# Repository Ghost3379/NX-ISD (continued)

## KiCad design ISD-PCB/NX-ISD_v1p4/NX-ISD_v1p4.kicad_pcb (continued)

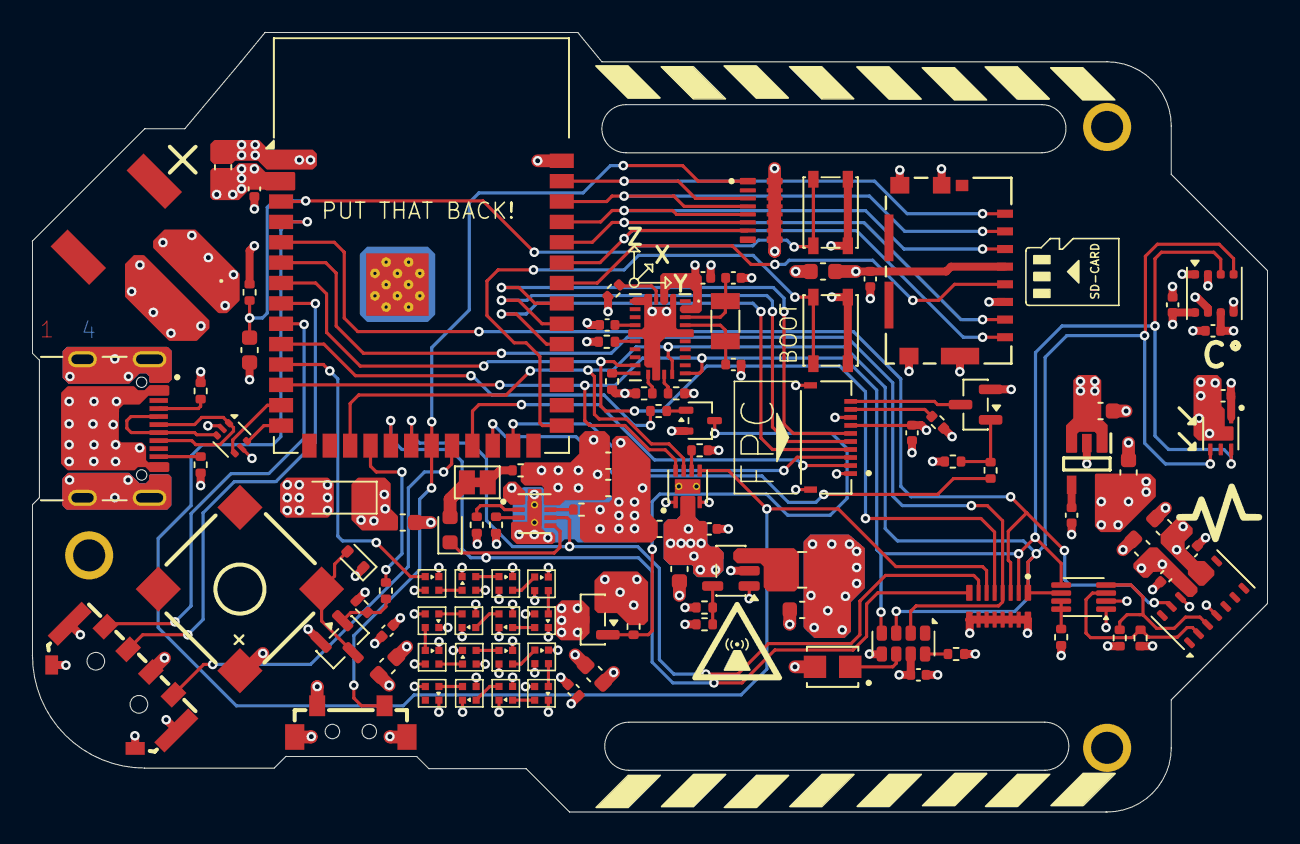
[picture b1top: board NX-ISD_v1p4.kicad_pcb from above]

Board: 4 copper layers, 77.0 x 48.6 mm, 109 parts (0 on the bottom side), 86 nets.

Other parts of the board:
XYZ: n/a; XYZ_DOF_symbol

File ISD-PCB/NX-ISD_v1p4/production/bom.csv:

Designator,Footprint,Quantity,Value,LCSC Part #
B1,BUZ-SMD_4P-L8.5-W8.5-BR-1,1,SMD-8503-3627-16Ω,C2685545
"C1, C10, C16, C26, C4, C9",0603,6,1u,
"C11, C24, C27, C33, C6",0603,5,10u,
"C12, C13, C17, C18, C19, C20, C21, C25, C28, C29, C30, C31, C34, C36",0402,14,100n,
"C2, C32, C35, C37",0603,4,4.7u,
"C22, C23",0402,2,22p,
C3,0402,1,10n,
C5,CAPCP3225X100N,1,CPH3225A,
D1,D_SOD-123,1,NRVB230LSFT1G,
D2,0603,1,ORANGE,
D3,D_SOD-523,1,1N4148WT,
"G1, G10, G11, G12, G13, G14, G15, G16, G2, G3, G4, G5, G6, G7, G8, G9",LED-SMD_4P-L1.0-W1.0-TL_XL-1010RGBC-WS2812B,16,XL-1010RGBC-WS2812B,C5349953
J1,SAMESKY_UJ20-C-H-G-SMT-1-P16-TR,1,UJ20-C-H-G-SMT-1-P16-TR,
J2,TE_1-2328702-0,1,1-2328702-0,
J3,105162-0001_MOL,1,1051620001,
L1,1008,1,2.2u,
P1,JST_S2B-PH-SM4-TB,1,S2B-PH-SM4-TB,
Q1,SOT-323_SC-70,1,BC847W,
Q2,SOT-23,1,AO3401A,
"Q3, Q4",SOT-23,2,AO3400A,
"R1, R2",0402,2,5.1k,
"R10, R4",0402,2,100K,
"R11, R12",0402,2,4.7k,
"R13, R14, R16, R17, R18, R19, R24, R26, R29, R8",0402,10,10k,
R15,0402,1,200k,
"R23, R25",0402,2,220,
R27,0402,1,10,
R3,0402,1,453k,
R5,0402,1,27k,
R6,0402,1,499,
"R7, R9",0402,2,1k,
"RN1, RN2",RESCAXS50P400X160X55-16N,2,YC248-JR-074K7L,
S1,KEY-SMD_TS-1101VS-C-A-A,1,TS-1101VS-C-A-A,
S2,SW-SMD_TM-2025A,1,TM-2025A,C318949
SW1,SW_SPST_PTS810,1,BOOT,
SW2,SW_SPST_PTS810,1,RST,
TH1,0402,1,10k NTC,
U1,SOT23-5,1,RT9193-18GB,C27416
U10,SON65P200X200X65-7N,1,OPT3001DNPR,
U11,IC_BNO085,1,BNO085,
U12,MicroCrystal_C7_SON-8_1.5x3.2mm_P0.9mm,1,RV-3028-C7,
U13,ESP32-S3-WROOM-1,1,ESP32-S3-WROOM-1-N16R8,ESP32-S3-WROOM-1-N16R8
U2,SOT-666,1,USBLC6-2P6,
U3,SOT-23-5,1,TLV62568DBV,
U5,SON50P200X200X80-9N,1,BQ25170DSGR,
U6,SON50P200X200X80-9N,1,MAX17048G_T10,
U7,Bosch_LGA-8_3x3mm_P0.8mm_ClockwisePinNumbering,1,BME690,
U8,Maxim_OLGA-14_3.3x5.6mm_P0.8mm,1,MAX30102,
U9,VSSOP-8_2.3x2mm_P0.5mm,1,PCA9306,
XYZ,XYZ_DOF_symbol,1,n/a,
Y1,Crystal_SMD_3215-2Pin_3.2x1.5mm,1,32.768 kHz,

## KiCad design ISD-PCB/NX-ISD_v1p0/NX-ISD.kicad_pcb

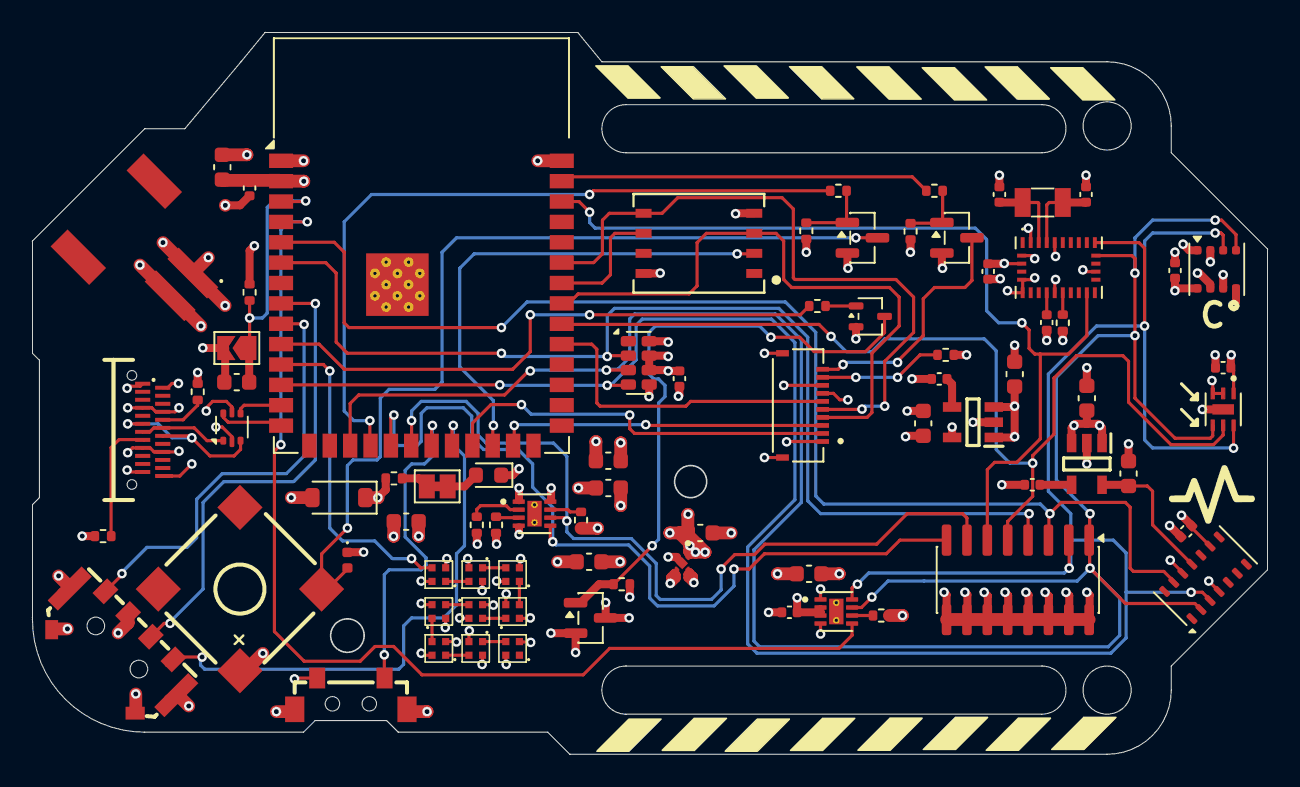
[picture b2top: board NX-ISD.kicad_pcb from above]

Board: 4 copper layers, 77.0 x 45.0 mm, 79 parts (0 on the bottom side), 66 nets.

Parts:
B1: SMD-8503-3627-16Ω; BUZ-SMD_4P-L8.5-W8.5-BR-1
C1, C5, C6, C7, C12, C17, C29, C30: 100n; C_0402_1005Metric
C2, C3, C4, C8, C9, C10, C13, C15, C20, C21: 1u; C_0603_1608Metric
C11, C14: 10n; C_0402_1005Metric
C16, C22: 10u; C_0603_1608Metric
C27, C28: 22p; C_0402_1005Metric
D1: ORANGE; LED_0603_1608Metric
D2: 1N4148WT; D_0402_1005Metric
D5: D_Schottky_Filled; D_SOD-123
G1, G2, G3, G4, G5, G6, G7, G8, G9: XL-1010RGBC-WS2812B; LED-SMD_4P-L1.0-W1.0-TL_XL-1010RGBC-WS2812B
J1: 1-2328702-0; TE_1-2328702-0
JP1: CUT2DISABLE; SolderJumper-2_P1.3mm_Bridged_Pad1.0x1.5mm
JP2: RESET; SolderJumper-2_P1.3mm_Open_TrianglePad1.0x1.5mm
P1: S2B-PH-SM4-TB; JST_S2B-PH-SM4-TB
Q1, Q4: AO3400A; SOT-23
Q2: AO3401A; SOT-23
Q3: BC847W; SOT-323_SC-70
R1, R9: 5.1k; R_0402_1005Metric
R2: 3K3; R_0402_1005Metric
R3, R4, R12, R14, R17: 10k; R_0402_1005Metric
R5, R10, R15: 220; R_0402_1005Metric
R6: 100K; R_0402_1005Metric
R8: 27k; R_0402_1005Metric
R11: 500; R_0402_1005Metric
R13: 1k; R_0402_1005Metric
RN1: 8x4.7k; SOIC-16_3.9x9.9mm_P1.27mm
S1: TS-1101VS-C-A-A; KEY-SMD_TS-1101VS-C-A-A
TH1: 10k; R_0402_1005Metric
U1: ESP32-S3-WROOM-1
U2: NCP167BMX330TBG; VREG_NCP167BMX330TBG
U3: MAX17048G_T10; SON50P200X200X80-9N
U4: RV-3028-C7; MicroCrystal_C7_SON-8_1.5x3.2mm_P0.9mm
U5: MAX30102; Maxim_OLGA-14_3.3x5.6mm_P0.8mm
U6: BME690; Bosch_LGA-8_3x3mm_P0.8mm_ClockwisePinNumbering
U7: TM-2025A; SW-SMD_TM-2025A
U8: BQ25170DSGR; SON50P200X200X80-9N
U9: RT9193-28GB; SOT23-5
U10: BNO085; IC_BNO085
U11: HYCW275-USBC24-050B; USB-C-SMD_HYCW275-USBC24-050B
U12: OPT3001DNPR; SON65P200X200X65-7N
U13: RT9193-18GB; SOT23-5
U14: ZDSD02GLGEAG; LGA-8_L8.0-W6.0-P1.27-TL_ZDSD02GLGEAG
U15: USBLC6-2P6; SOT-666
Y2: 32.768; Crystal_SMD_3215-2Pin_3.2x1.5mm

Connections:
+1V8: C15.1, U5.11 (VDD), U13.5 (VOUT)
+2V8: C10.1, J1.7, U9.5 (VOUT)
+3V3: B1.1, C1.1, C3.1, C5.1, C6.1, C9.1, C12.1, C13.1, C16.1, C17.1, C30.1, D2.1 (K), R3.1, R15.1, R17.1, RN1.9 (R8.2), RN1.10 (R7.2), RN1.11 (R6.2), RN1.12 (R5.2), RN1.13 (R4.2), RN1.14 (R3.2), RN1.15 (R2.2), RN1.16 (R1.2), U1.2 (3V3), U2.1 (OUT), U4.6 (VBACKUP), U4.7 (VDD), U5.9 (VLED+), U6.2 (CSB), U6.6 (VDDIO), U6.8 (VDD), U9.1 (VIN), U9.3 (EN), U10.3 (VDD), U10.28 (VDDIO), U12.1 (VDD), U13.1 (VIN), U13.3 (EN), U14.8 (VDD)
/Logic section/!ALERT: U1.4 (IO4), U3.5 (~ALERT)
/Logic section/!INT_ALS: RN1.5 (R5.1), U1.32 (IO39), U12.5 (INT)
/Logic section/!INT_H: RN1.6 (R6.1), U1.38 (IO2), U10.14 (~H_INT)
/Logic section/!INT_HR: RN1.3 (R3.1), U1.5 (IO5), U5.13 (~INT)
/Logic section/!INT_RTC: RN1.4 (R4.1), U1.6 (IO6), U4.2 (~INT)
/Logic section/BAT_STAT: RN1.8 (R8.1), U1.19 (IO11), U8.5 (STAT)
/Logic section/BTN: S1.1, U1.21 (IO13)
/Logic section/CS_SD: U1.24 (IO47), U14.2 (DATA3)
/Logic section/CS_TFT: J1.3, U1.25 (IO48)
/Logic section/D+: U1.14 (USB_D+), U15.6 (I/O1)
/Logic section/D-: U1.13 (USB_D-), U15.4 (I/O2)
/Logic section/DOUT_NPM: G1.4 (DIN), U1.11 (IO18)
/Logic section/EN: C8.1, JP2.1 (A), R3.2, U1.3 (EN)
/Logic section/LEVER_LEFT: U1.22 (IO14), U7.1
/Logic section/LEVER_PUSH: U1.8 (IO15), U7.3
/Logic section/LEVER_RIGHT: U1.9 (IO16), U7.2
/Logic section/MISO: U1.34 (IO41), U14.6 (DAT0)
/Logic section/MOSI: J1.5, U1.35 (IO42), U14.5 (CMD)
/Logic section/PWM_TFT: R10.2, U1.39 (IO1)
/Logic section/PWR_NPM: R13.2, U1.10 (IO17)
/Logic section/RS: J1.2, U1.23 (IO21)
/Logic section/RST: J1.6, U1.31 (IO38)
/Logic section/SCK: J1.4, U1.33 (IO40), U14.3 (CLK)
/Logic section/USB_DETECT: RN1.7 (R7.1), U1.20 (IO12), U8.6 (~PG)
/Peripherie/BUZZER: R5.2, U1.18 (IO10)
/Power section/CC1: R1.1, U11.A5 (CC1)
/Power section/CC2: R9.1, U11.B5 (CC2)
/Power section/USB_P: D5.2 (A), U11.A4 (VBUS), U11.A9 (VBUS), U11.B4 (VBUS), U11.B9 (VBUS), U15.5 (VBUS)
/Power section/U_D+: U11.A6 (DP1), U11.B6 (DP2), U15.1 (I/O1)
/Power section/U_D-: U11.A7 (DN1), U11.B7 (DN2), U15.3 (I/O2)
/Sernsor section/SCL_1: RN1.1 (R1.1), U1.17 (IO9), U3.7 (SCL), U4.3 (SCL), U5.2 (SCL), U6.4 (SCK), U10.19 (H_SCL/SCK/RX), U12.4 (SCL)
/Sernsor section/SDA_1: RN1.2 (R2.1), U1.12 (IO8), U3.8 (SDA), U4.4 (SDA), U5.3 (SDA), U6.3 (SDI), U10.20 (H_SDA/H_MISO/TX), U12.6 (SDA)
GND: C1.2, C2.2, C3.2, C4.2, C5.2, C6.2, C7.2, C8.2, C9.2, C10.2, C11.2, C12.2, C13.2, C14.2, C15.2, C16.2, C17.2, C20.2, C21.2, C22.2, C27.2, C28.2, C29.1, C30.2, D1.1 (K), G1.3 (GND), G2.3 (GND), G3.3 (GND), G4.3 (GND), G5.3 (GND), G6.3 (GND), G7.3 (GND), G8.3 (GND), G9.3 (GND), J1.1, J1.8, J1.S1 (SHIELD), J1.S2 (SHIELD), JP2.2 (B), P1.2, Q1.2 (S), Q3.2 (E), Q4.2 (S), R1.2, R4.2, R6.1, R8.1, R9.2, R11.1, R14.2, S1.2, S1.3, S1.4, TH1.2, U1.1 (GND), U1.40 (GND), U1.41 (GND), U2.2 (GND), U2.5 (EPAD), U3.1 (CTG), U3.4 (GND), U3.9 (EP), U3.10, U3.11, U4.5 (VSS), U4.8 (EVI), U5.4 (PGND), U5.12 (GND), U6.1 (GND), U6.5 (SDO), U6.7 (GND), U7.4, U7.5, U7.6, U7.7, U7.8, U8.4 (GND), U8.9 (EXP), U8.10, U8.11, U9.2 (GND), U10.2 (GND), U10.5 (PS1), U10.6 (PS0/WAKE), U10.10 (CLKSEL0), U10.17 (SA0/H_MOSI), U10.25 (GNDIO), U11.A1 (GND), U11.A12 (GND), U11.B1 (GND), U11.B12 (GND), U12.2 (ADDR), U12.3 (GND), U12.7 (EXP), U13.2 (GND), U14.4 (GND), U15.2 (GND)
unnamed: D1.2 (A), JP1.2 (B)
unnamed: B1.4, D2.2 (A), Q1.3 (D)
unnamed: G1.1 (DOUT), G2.4 (DIN)
unnamed: G2.1 (DOUT), G3.4 (DIN)
unnamed: G3.1 (DOUT), G4.4 (DIN)
unnamed: G4.1 (DOUT), G5.4 (DIN)
unnamed: G5.1 (DOUT), G6.4 (DIN)
unnamed: G6.1 (DOUT), G7.4 (DIN)
unnamed: G7.1 (DOUT), G8.4 (DIN)
unnamed: G8.1 (DOUT), G9.4 (DIN)
unnamed: J1.9, R15.2
unnamed: JP1.1 (A), R2.2
unnamed: Q1.1 (G), R4.1, R5.1
unnamed: Q2.1 (G), Q3.3 (C), R12.1
unnamed: Q3.1 (B), R13.1
unnamed: J1.10, Q4.3 (D)
unnamed: Q4.1 (G), R10.1, R14.1
unnamed: R6.2, U3.6 (QSTRT)
unnamed: R11.2, U8.2 (ISET)
unnamed: TH1.1, U8.3 (TS)
unnamed: R8.2, U8.7 (VSET)
unnamed: C11.1, U9.4 (BP)
unnamed: C29.2, U10.9 (CAP)
unnamed: C28.1, U10.27 (XIN32), Y2.1
unnamed: C27.1, U10.26 (XOUT32/CLKSEL1), Y2.2
unnamed: R17.2, U10.11 (~RST)
unnamed: C14.1, U13.4 (BP)
VBAT: C2.1, C4.1, C7.1, C21.1, C22.1, P1.1, Q2.3 (D), R12.2, U2.3 (EN), U2.4 (IN), U3.2 (CELL), U3.3 (VDD), U8.8 (OUT)
VBUS: C20.1, D5.1 (K), R2.1, U8.1 (IN)
VN: G1.2 (VDD), G2.2 (VDD), G3.2 (VDD), G4.2 (VDD), G5.2 (VDD), G6.2 (VDD), G7.2 (VDD), G8.2 (VDD), G9.2 (VDD), Q2.2 (S)

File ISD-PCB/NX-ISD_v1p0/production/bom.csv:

Designator,Footprint,Quantity,Value, Distributor,DONE
B1,BUZ-SMD_4P-L8.5-W8.5-BR-1,1,SMD-8503-3627-16Ω,lcsc,X
"C1, C12, C17, C29, C30, C5, C6, C7",0402,8,100n,digikey,x
"C10, C13, C15, C2, C3, C4, C9, C20, C21, C8",0603,10,1u,digikey,x
"C11, C14",0402,2,10n,digikey,x
"C16, C22",0603,2,10u,digikey,x
"C27, C28",0402,2,22p,digikey,x
D1,0603,1,ORANGE,lcsc,x
D2,0402,1,1N4148WT,mouser,x
D5,D_SOD-123,1,D_Schottky_Filled,mouser,x
"G1, G2, G3, G4, G5, G6, G7, G8, G9",LED-SMD_4P-L1.0-W1.0-TL_XL-1010RGBC-WS2812B,9,XL-1010RGBC-WS2812B,lcsc,X
J1,TE_1-2328702-0,1,1-2328702-0,mouser,x
"Q1, Q4",SOT-23,2,AO3400A,mouser,x
Q2,SOT-23,1,AO3401A,mouser,x
Q3,SOT-323_SC-70,1,BC847W,mouser,x
"R1, R9",0402,2,5.1k,digikey,x
"R10, R15, R5",0402,3,220,digikey,x
R11,0402,1,500,digikey,x
"R12, R14, R17, R3, R4",0402,6,10k,digikey,x
TH1,0402,1,10k,digikey,x
R13,0402,1,1k,digikey,x
R2,0402,1,3K3,digikey,x
R6,0402,1,100K,digikey,x
R8,0402,1,27k,digikey,x
RN1,SOIC-16_3.9x9.9mm_P1.27mm,1,8x4.7k,mouser,x
S1,KEY-SMD_TS-1101VS-C-A-A,1,TS-1101VS-C-A-A,lcsc,X
U1,ESP32-S3-WROOM-1,1,ESP32-S3-WROOM-1,mouser,x
U10,IC_BNO085,1,BNO085,digikey,x
U11,USB-C-SMD_HYCW275-USBC24-050B,1,HYCW275-USBC24-050B,lcsc,x
U12,SON65P200X200X65-7N,1,OPT3001DNPR,mouser,x
U13,SOT23-5,1,RT9193-18GB,lcsc,X
U14,LGA-8_L8.0-W6.0-P1.27-TL_ZDSD02GLGEAG,1,ZDSD02GLGEAG,lcsc,X
U15,SOT-666,1,USBLC6-2P6,mouser,x
U2,VREG_NCP167BMX330TBG,1,NCP167BMX330TBG,mouser,x
U3,SON50P200X200X80-9N,1,MAX17048G_T10,lcsc,x
U4,MicroCrystal_C7_SON-8_1.5x3.2mm_P0.9mm,1,RV-3028-C7,digikey,x
U5,Maxim_OLGA-14_3.3x5.6mm_P0.8mm,1,MAX30102,mouser,x
U6,Bosch_LGA-8_3x3mm_P0.8mm_ClockwisePinNumbering,1,BME690,mouser,x
U7,SW-SMD_TM-2025A,1,TM-2025A,lcsc,X
U8,SON50P200X200X80-9N,1,BQ25170DSGR,lcsc,X
U9,SOT23-5,1,RT9193-28GB,lcsc,X
Y2,Crystal_SMD_3215-2Pin_3.2x1.5mm,1,32.768,digikey,x

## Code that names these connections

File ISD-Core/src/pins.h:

#pragma once

// ==============================================================================
// NX-ISD Hardware Revision Selection
// ==============================================================================
// Define the target hardware revision:
//   NX_ISD_HW_V1P4 : v1.4 Production PCB (Dedicated 3.3V Display SPI, 4-bit SDMMC, updated GPIOs)
//   NX_ISD_HW_V1P3 : v1.3 Prototype PCB (Shared SPI, TXB0106 level shifter, ZDSD NAND Flash)
//
// Can be selected via platformio.ini build_flags (e.g. -D NX_ISD_HW_V1P4 or -D NX_ISD_HW_V1P3).
// If neither is passed by compiler flag, defaults to v1.4 below:
#if !defined(NX_ISD_HW_V1P3) && !defined(NX_ISD_HW_V1P4)
  #define NX_ISD_HW_V1P4
#endif

// ==============================================================================
// 1. Common Hardware Pins (Identical on v1.3 & v1.4)
// ==============================================================================

// I2C Bus (Wire @ 400kHz Fast Mode)
#define I2C_SDA         8
#define I2C_SCL         9

// Power Control
#define PWR_NPM         17  // Switched VN PMOS High-Side Gate (Active HIGH via Q1)

// Peripherals
#define NPM             18  // NeoPixel Matrix Serial Data Out (G1 DIN stream)
#define BUZZER          10  // Electromagnetic Buzzer PWM Gate (Q3 AO3400A)

// Charging & USB Detection
#define USB_DETECT      12  // USB 5V VBUS Presence Divider (HIGH when plugged in)
#define BAT_STAT        11  // BQ25170 Charger Status (LOW = Charging, HIGH/Hi-Z = Done)

// Primary Button
#define BTN             13  // Main User Tactile Push-Button (External pull-up)

// Sensors & Clocks (Common Interrupt Lines)
#define INT_RTC         6   // RV-3028-C7 Alarm/Timer Interrupt (Active LOW)
#define INT_HR          5   // MAX30102 PPG Sample FIFO Ready Interrupt (Active LOW)
#define ALERT           4   // MAX17048 Fuel Gauge Battery Alert (Active LOW)

// Navigation Center Push
#define LEVER_PUSH      15  // Navigation Lever Center Push (Active LOW)


// ==============================================================================
// 2. Hardware Revision Specific Pin Mappings
// ==============================================================================

#if defined(NX_ISD_HW_V1P4)
// ------------------------------------------------------------------------------
// Hardware Revision v1.4 (Production Board)
// ------------------------------------------------------------------------------
#define HW_REVISION_STRING "v1.4"

// Display SPI Bus (Dedicated 3.3V Bus directly to J2 - No TXB0106 Level Shifter)
#define TFT_SCK         38  // Display Serial Clock (FSPI SCK)
#define TFT_MOSI        39  // Display Master-Out-Slave-In (FSPI MOSI)
#define TFT_RS          21  // Display Command / Data (DC)
#define TFT_RST         40  // Display Hardware Reset (Active LOW)
#define CS_TFT          48  // Display Chip Select (Active LOW)
#define TFT_PWM         47  // Backlight PWM (Q4 AO3400A Gate)

// Display Bus Configuration
// Direct 3.3V connection allows full 40 MHz SPI write clock (~43.5 FPS)
#define TFT_SPI_FREQ    40000000
#define TFT_BUS_SHARED  false // Dedicated SPI bus to display

// Display SPI Bus Compatibility Aliases
#define SPI_SCK         TFT_SCK
#define SPI_MOSI        TFT_MOSI
#define SPI_MISO        (-1) // Display is write-only; no MISO needed on dedicated bus

// MicroSD Storage (Dedicated 4-Bit SDMMC / SPI via GPIO Matrix)
#define SD_CLK          41
#define SD_CMD          43  // TXD0 pin on ESP32-S3
#define SD_DAT0         44  // RXD0 pin on ESP32-S3
#define SD_DAT1         42
#define SD_DAT2         1
#define SD_DAT3         2   // CS_SD in 1-bit SPI fallback mode
#define CS_SD           SD_DAT3

// Navigation Lever (Physical orientation corrected on v1.4 PCB layout)
#define LEVER_LEFT      14  // Lever tilted left
#define LEVER_RIGHT     16  // Lever tilted right

// Interrupts
#define INT_DOF         7   // BNO085 9-DOF IMU Motion Interrupt (Active LOW)
#define INT_ALS         (-1)// OPT3001 polled over I2C; interrupt omitted on v1.4

#elif defined(NX_ISD_HW_V1P3)
// ------------------------------------------------------------------------------
// Hardware Revision v1.3 (Prototype Board)
// ------------------------------------------------------------------------------
#define HW_REVISION_STRING "v1.3"

// Shared High-Speed SPI Bus (Display via TXB0106 Level Shifter + ZDSD NAND Flash)
#define SPI_SCK         40
#define SPI_MISO        41
#define SPI_MOSI        42

// Display Pins
#define CS_TFT          48
#define TFT_RS          21  // Command / Data
#define TFT_RST         38
#define TFT_PWM         1   // Backlight PWM
#define CS_SD           47  // ZDSD NAND Flash Chip Select

// Display SPI Aliases
#define TFT_SCK         SPI_SCK
#define TFT_MOSI        SPI_MOSI

// Display Bus Configuration & Bandwidth Restriction:
// NOTE: The TXB0106 auto-direction-sensing level shifter (U15) on v1.3 cannot hold up
// with the intended 40 MHz SPI clock. Signal edge rounding, propagation delay, and capacitive
// loading cause severe pixel jitter, missed clock cycles, and periodic display corruption at 40 MHz.
// We strictly cap v1.3 to 16 MHz for clean, reliable, flicker-free operation (~17.4 FPS).
#define TFT_SPI_FREQ    16000000
#define TFT_BUS_SHARED  true  // Shared SPI bus with ZDSD NAND Flash

// Navigation Lever (Rotated 180° assembly on physical v1.3 carrier board)
#define LEVER_LEFT      16  // Physical Left maps to GPIO 16
#define LEVER_RIGHT     14  // Physical Right maps to GPIO 14

// Interrupts
#define INT_DOF         2   // BNO085 9-DOF IMU Motion Interrupt (Active LOW)
#define INT_ALS         39  // OPT3001 Light Sensor Interrupt (Active LOW)

#endif
